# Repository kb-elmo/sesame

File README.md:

# Sesame

[![CC BY-NC-SA 4.0][cc-by-nc-sa-shield]][cc-by-nc-sa]

### Alice like ergo keyboard using only THT parts

### Partslist
 |Count|Part|Reference|LCSC Part #|
 |-|-|-|-|
 |1|ATmega32A 40 pin DIP (32L works too)|U1|C12703|
 |1|40 pin DIP socket (optional but highly recommended)|U1|C2332|
 |1|USB4085-GF-A USB Type-C socket|USB1|
 |1|500 mA polyfuse|F1|C207122|
 |2|6mm momentary push buttons|Boot,Reset|C620202|
 |1|16 MHz quartz crystal|XTAL1|C16212|
 |1|4.7 uF electrolytic capacitor|C1|C47879|
 |2|100 nF ceramic disk capacitor|C2,C3|C254092|
 |2|22 pF ceramic disk capacitor|C4,C5|C254096|
 |1|1.5 kΩ resistor|R1|C58620|
 |2|68 Ω resistor|R2,R3|C714279|
 |2|5.1 kΩ resistor|R4,R5|C714593|
 |1|10 kΩ resistor|R6|C119347|
 |2|3.6 V zener diode (DO-35 BZX55C3V6)|D1,D2|C2508|
 |66|universal switching diode (DO-35 1N4148)|D3-D68|C14516|
 
 The USB port can be found here:  
https://www.digikey.com/en/products/detail/gct/USB4085-GF-A/9859733

-----

This work is licensed under a
[Creative Commons Attribution-NonCommercial-ShareAlike 4.0 International License][cc-by-nc-sa].

[![CC BY-NC-SA 4.0][cc-by-nc-sa-image]][cc-by-nc-sa]

[cc-by-nc-sa]: http://creativecommons.org/licenses/by-nc-sa/4.0/
[cc-by-nc-sa-image]: https://licensebuttons.net/l/by-nc-sa/4.0/88x31.png
[cc-by-nc-sa-shield]: https://img.shields.io/badge/License-CC%20BY--NC--SA%204.0-lightgrey.svg

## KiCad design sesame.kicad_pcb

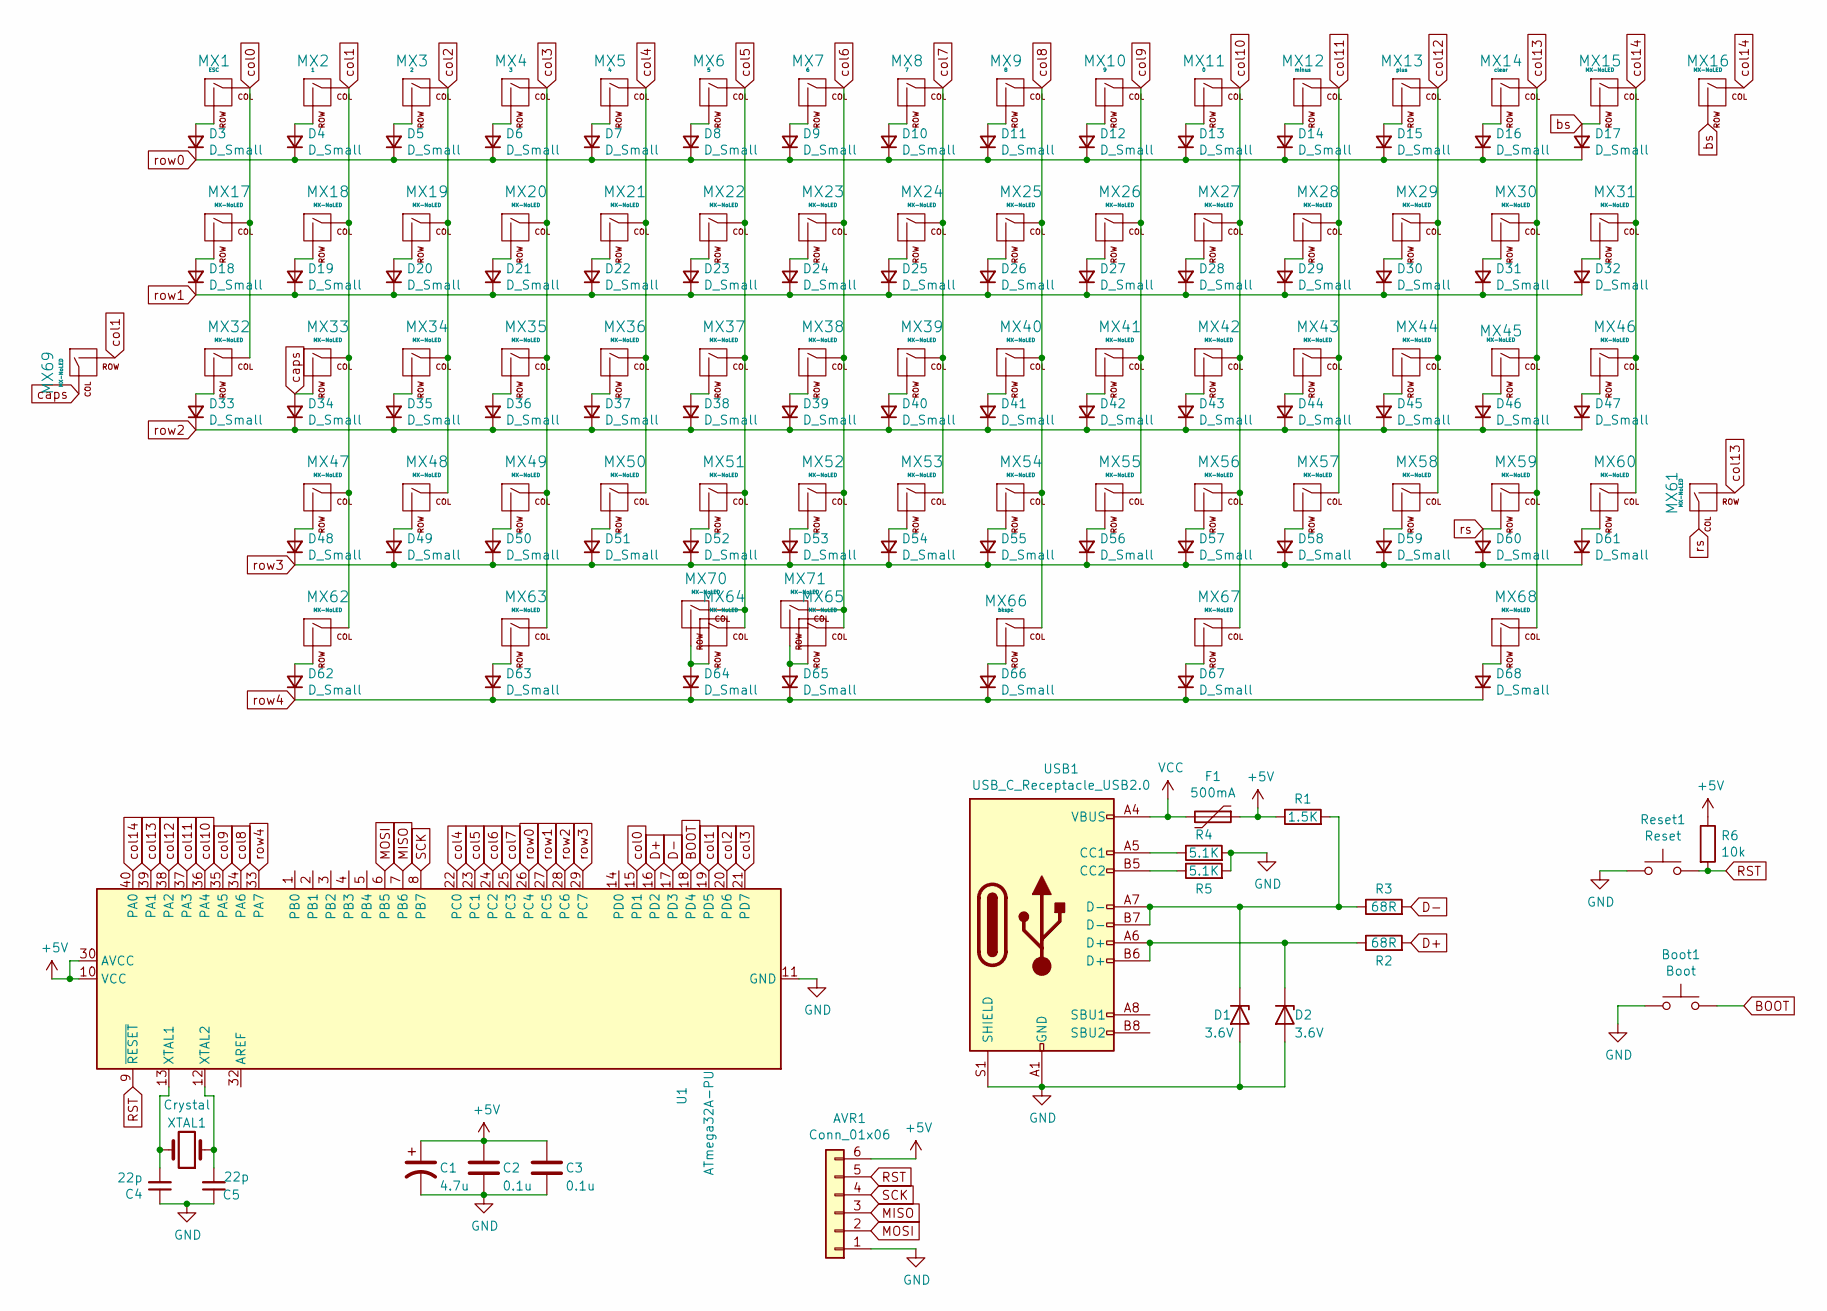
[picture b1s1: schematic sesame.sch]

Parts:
AVR1: Conn_01x06; PinHeader_1x06_P2.54mm_Vertical
Boot1: Boot; SW_PUSH_6mm
C1: 4.7u; CP_Radial_D4.0mm_P1.50mm
C2, C3: 0.1u; C_Disc_D5.0mm_W2.5mm_P5.00mm
C4, C5: 22p; C_Disc_D5.0mm_W2.5mm_P2.50mm
D1, D2: 3.6V; D_DO-35_SOD27_P7.62mm_Horizontal
D3, D4, D5, D6, D7, D8, D9, D10, D11, D12, D13, D14, D15, D16, D17, D18, D19, D20, D21, D22, D23, D24, D25, D26, D27, D28, D29, D30, D31, D32, D33, D34, D35, D36, D37, D38, D39, D40, D41, D42, D43, D44, D45, D46, D47, D48, D49, D50, D51, D52, D53, D54, D55, D56, D57, D58, D59, D60, D61, D62, D63, D64, D65, D66, D67, D68: D_Small; D_DO-35_SOD27_P7.62mm_Horizontal
F1: 500mA; Fuse_Littelfuse_395Series
MX1: ESC; MXOnly-1U-NoLED
MX2: 1; MXOnly-1U-NoLED
MX3: 2; MXOnly-1U-NoLED
MX4: 3; MXOnly-1U-NoLED
MX5: 4; MXOnly-1U-NoLED
MX6: 5; MXOnly-1U-NoLED
MX7: 6; MXOnly-1U-NoLED
MX8: 7; MXOnly-1U-NoLED
MX9: 8; MXOnly-1U-NoLED
MX10: 9; MXOnly-1U-NoLED
MX11: 0; MXOnly-1U-NoLED
MX12: minus; MXOnly-1U-NoLED
MX13: plus; MXOnly-1U-NoLED
MX14: clear; MXOnly-1U-NoLED
MX15: MX-NoLED; MXOnly-2U-NoLED
MX16, MX17, MX19, MX20, MX21, MX22, MX23, MX24, MX25, MX26, MX27, MX28, MX29, MX30, MX32, MX34, MX35, MX36, MX37, MX38, MX39, MX40, MX41, MX42, MX43, MX44, MX45, MX48, MX49, MX50, MX51, MX52, MX53, MX54, MX55, MX56, MX57, MX58, MX60, MX67, MX68, MX71: MX-NoLED; MXOnly-1U-NoLED
MX18, MX31, MX62, MX63: MX-NoLED; MXOnly-1.5U-NoLED
MX33, MX59: MX-NoLED; MXOnly-1.75U-NoLED
MX46, MX70: MX-NoLED; MXOnly-2.25U-ReversedStabilizers-NoLED
MX47: MX-NoLED; MXOnly-2.25U-NoLED
MX61: MX-NoLED; MXOnly-2.75U-NoLED
MX64: MX-NoLED; MXOnly-2U-ReversedStabilizers-NoLED
MX65, MX69: MX-NoLED; MXOnly-1.25U-NoLED
MX66: bkspc; MXOnly-2.25U-ReversedStabilizers-NoLED
R1: 1.5K; R_Axial_DIN0207_L6.3mm_D2.5mm_P10.16mm_Horizontal
R2, R3: 68R; R_Axial_DIN0207_L6.3mm_D2.5mm_P10.16mm_Horizontal
R4, R5: 5.1K; R_Axial_DIN0207_L6.3mm_D2.5mm_P10.16mm_Horizontal
R6: 10k; R_Axial_DIN0207_L6.3mm_D2.5mm_P10.16mm_Horizontal
Reset1: Reset; SW_PUSH_6mm
U1: ATmega32A-PU; DIP-40_W15.24mm
USB1: USB_C_Receptacle_USB2.0; USB_C_GCT_USB4085
XTAL1: Crystal; Crystal_HC49-4H_Vertical

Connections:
+5V: AVR1.6, C1.1, C2.1, C3.1, F1.1, R1.1, R6.1, U1.10 (VCC), U1.30 (AVCC)
BOOT: Boot1.2, U1.18 (PD4); also elsewhere on the board
D+: R2.2, U1.16 (PD2)
D-: R3.2, U1.17 (PD3)
GND: AVR1.1, Boot1.1, C1.2, C2.2, C3.2, C4.1, C5.1, D1.2 (A), D2.2 (A), R4.2, R5.2, Reset1.1, U1.11 (GND), U1.31 (GND), USB1.A1 (GND), USB1.A12 (GND), USB1.B1 (GND), USB1.B12 (GND), USB1.S1 (SHIELD); also elsewhere on the board
MISO: AVR1.3, U1.7 (PB6)
MOSI: AVR1.2, U1.6 (PB5)
unnamed: C4.2, U1.13 (XTAL1), XTAL1.2
unnamed: C5.2, U1.12 (XTAL2), XTAL1.1
unnamed: D1.1 (K), R1.2, R3.1, USB1.A7 (D-), USB1.B7 (D-)
unnamed: D2.1 (K), R2.1, USB1.A6 (D+), USB1.B6 (D+)
unnamed: D3.2 (A), MX1.2 (ROW)
unnamed: D4.2 (A), MX2.2 (ROW)
unnamed: D5.2 (A), MX3.2 (ROW)
unnamed: D6.2 (A), MX4.2 (ROW)
unnamed: D7.2 (A), MX5.2 (ROW)
unnamed: D8.2 (A), MX6.2 (ROW)
unnamed: D9.2 (A), MX7.2 (ROW)
unnamed: D10.2 (A), MX8.2 (ROW)
unnamed: D11.2 (A), MX9.2 (ROW)
unnamed: D12.2 (A), MX10.2 (ROW)
unnamed: D13.2 (A), MX11.2 (ROW)
unnamed: D14.2 (A), MX12.2 (ROW)
unnamed: D15.2 (A), MX13.2 (ROW)
unnamed: D16.2 (A), MX14.2 (ROW)
unnamed: D18.2 (A), MX17.2 (ROW)
unnamed: D19.2 (A), MX18.2 (ROW)
unnamed: D20.2 (A), MX19.2 (ROW)
unnamed: D21.2 (A), MX20.2 (ROW)
unnamed: D22.2 (A), MX21.2 (ROW)
unnamed: D23.2 (A), MX22.2 (ROW)
unnamed: D24.2 (A), MX23.2 (ROW)
unnamed: D25.2 (A), MX24.2 (ROW)
unnamed: D26.2 (A), MX25.2 (ROW)
unnamed: D27.2 (A), MX26.2 (ROW)
unnamed: D28.2 (A), MX27.2 (ROW)
unnamed: D29.2 (A), MX28.2 (ROW)
unnamed: D30.2 (A), MX29.2 (ROW)
unnamed: D31.2 (A), MX30.2 (ROW)
unnamed: D32.2 (A), MX31.2 (ROW)
unnamed: D33.2 (A), MX32.2 (ROW)
unnamed: D35.2 (A), MX34.2 (ROW)
unnamed: D36.2 (A), MX35.2 (ROW)
unnamed: D37.2 (A), MX36.2 (ROW)
unnamed: D38.2 (A), MX37.2 (ROW)
unnamed: D39.2 (A), MX38.2 (ROW)
unnamed: D40.2 (A), MX39.2 (ROW)
unnamed: D41.2 (A), MX40.2 (ROW)
unnamed: D42.2 (A), MX41.2 (ROW)
unnamed: D43.2 (A), MX42.2 (ROW)
unnamed: D44.2 (A), MX43.2 (ROW)
unnamed: D45.2 (A), MX44.2 (ROW)
unnamed: D46.2 (A), MX45.2 (ROW)
unnamed: D47.2 (A), MX46.2 (ROW)
unnamed: D48.2 (A), MX47.2 (ROW)
unnamed: D49.2 (A), MX48.2 (ROW)
unnamed: D50.2 (A), MX49.2 (ROW)
unnamed: D51.2 (A), MX50.2 (ROW)
unnamed: D52.2 (A), MX51.2 (ROW)
unnamed: D53.2 (A), MX52.2 (ROW)
unnamed: D54.2 (A), MX53.2 (ROW)
unnamed: D55.2 (A), MX54.2 (ROW)
unnamed: D56.2 (A), MX55.2 (ROW)
unnamed: D57.2 (A), MX56.2 (ROW)
unnamed: D58.2 (A), MX57.2 (ROW)
unnamed: D59.2 (A), MX58.2 (ROW)
unnamed: D61.2 (A), MX60.2 (ROW)
unnamed: D62.2 (A), MX62.2 (ROW)
unnamed: D63.2 (A), MX63.2 (ROW)
unnamed: D64.2 (A), MX64.2 (ROW), MX70.2 (ROW)
unnamed: D65.2 (A), MX65.2 (ROW), MX71.2 (ROW)
unnamed: D66.2 (A), MX66.2 (ROW)
unnamed: D67.2 (A), MX67.2 (ROW)
unnamed: D68.2 (A), MX68.2 (ROW)
unnamed: R4.1, USB1.A5 (CC1)
unnamed: R5.1, USB1.B5 (CC2)
RST: AVR1.5, R6.2, Reset1.2, U1.9 (~RESET); also elsewhere on the board
SCK: AVR1.4, U1.8 (PB7)
VCC: F1.2, USB1.A4 (VBUS), USB1.A9 (VBUS), USB1.B4 (VBUS), USB1.B9 (VBUS)
bs: D17.2 (A), MX15.2 (ROW), MX16.2 (ROW)
caps: D34.2 (A), MX33.2 (ROW), MX69.1 (COL)
col0: MX1.1 (COL), MX17.1 (COL), MX32.1 (COL), U1.15 (PD1)
col1: MX2.1 (COL), MX18.1 (COL), MX33.1 (COL), MX47.1 (COL), MX62.1 (COL), MX69.2 (ROW), U1.19 (PD5)
col2: MX3.1 (COL), MX19.1 (COL), MX34.1 (COL), MX48.1 (COL), U1.20 (PD6)
col3: MX4.1 (COL), MX20.1 (COL), MX35.1 (COL), MX49.1 (COL), MX63.1 (COL), U1.21 (PD7)
col4: MX5.1 (COL), MX21.1 (COL), MX36.1 (COL), MX50.1 (COL), U1.22 (PC0)
col5: MX6.1 (COL), MX22.1 (COL), MX37.1 (COL), MX51.1 (COL), MX64.1 (COL), MX70.1 (COL), U1.23 (PC1)
col6: MX7.1 (COL), MX23.1 (COL), MX38.1 (COL), MX52.1 (COL), MX65.1 (COL), MX71.1 (COL), U1.24 (PC2)
col7: MX8.1 (COL), MX24.1 (COL), MX39.1 (COL), MX53.1 (COL), U1.25 (PC3)
col8: MX9.1 (COL), MX25.1 (COL), MX40.1 (COL), MX54.1 (COL), MX66.1 (COL), U1.34 (PA6)
col9: MX10.1 (COL), MX26.1 (COL), MX41.1 (COL), MX55.1 (COL), U1.35 (PA5)
col10: MX11.1 (COL), MX27.1 (COL), MX42.1 (COL), MX56.1 (COL), MX67.1 (COL), U1.36 (PA4)
col11: MX12.1 (COL), MX28.1 (COL), MX43.1 (COL), MX57.1 (COL), U1.37 (PA3)
col12: MX13.1 (COL), MX29.1 (COL), MX44.1 (COL), MX58.1 (COL), U1.38 (PA2)
col13: MX14.1 (COL), MX30.1 (COL), MX45.1 (COL), MX59.1 (COL), MX61.2 (ROW), MX68.1 (COL), U1.39 (PA1)
col14: MX15.1 (COL), MX16.1 (COL), MX31.1 (COL), MX46.1 (COL), MX60.1 (COL), U1.40 (PA0)
row0: D3.1 (K), D4.1 (K), D5.1 (K), D6.1 (K), D7.1 (K), D8.1 (K), D9.1 (K), D10.1 (K), D11.1 (K), D12.1 (K), D13.1 (K), D14.1 (K), D15.1 (K), D16.1 (K), D17.1 (K), U1.26 (PC4)
row1: D18.1 (K), D19.1 (K), D20.1 (K), D21.1 (K), D22.1 (K), D23.1 (K), D24.1 (K), D25.1 (K), D26.1 (K), D27.1 (K), D28.1 (K), D29.1 (K), D30.1 (K), D31.1 (K), D32.1 (K), U1.27 (PC5)
row2: D33.1 (K), D34.1 (K), D35.1 (K), D36.1 (K), D37.1 (K), D38.1 (K), D39.1 (K), D40.1 (K), D41.1 (K), D42.1 (K), D43.1 (K), D44.1 (K), D45.1 (K), D46.1 (K), D47.1 (K), U1.28 (PC6)
row3: D48.1 (K), D49.1 (K), D50.1 (K), D51.1 (K), D52.1 (K), D53.1 (K), D54.1 (K), D55.1 (K), D56.1 (K), D57.1 (K), D58.1 (K), D59.1 (K), D60.1 (K), D61.1 (K), U1.29 (PC7)
row4: D62.1 (K), D63.1 (K), D64.1 (K), D65.1 (K), D66.1 (K), D67.1 (K), D68.1 (K), U1.33 (PA7)
rs: D60.2 (A), MX59.2 (ROW), MX61.1 (COL)

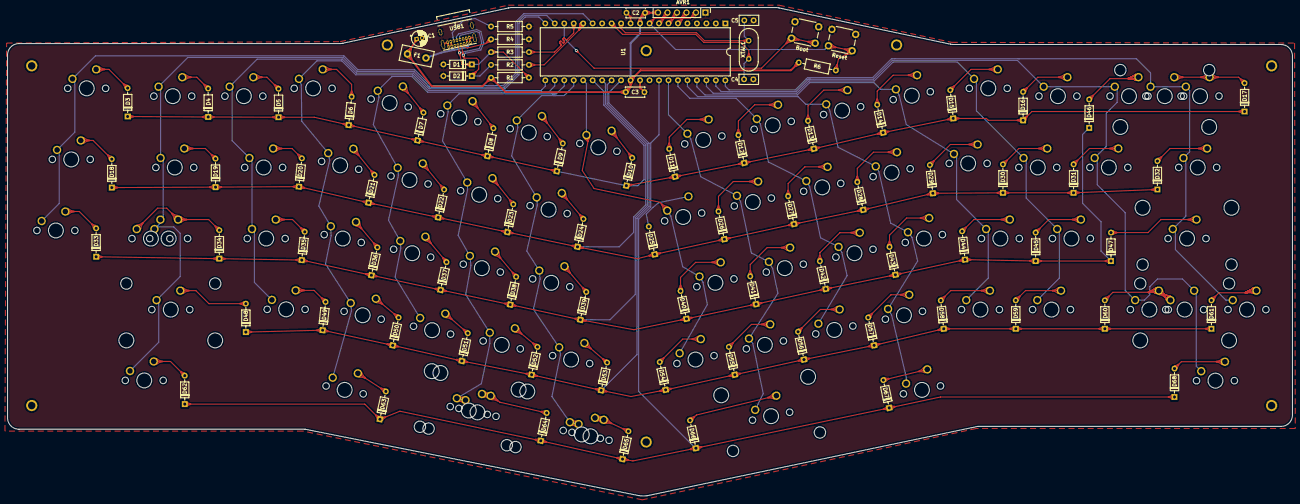
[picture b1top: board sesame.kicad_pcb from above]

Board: 2 copper layers, 344.4 x 130.9 mm, 157 parts (0 on the bottom side), 102 nets.

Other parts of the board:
Boot: Boot; SW_PUSH_6mm
Reset: Reset; SW_PUSH_6mm

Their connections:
BOOT: Boot.2; also elsewhere on the board
GND: Boot.1, Reset.1; also elsewhere on the board
RST: Reset.2; also elsewhere on the board

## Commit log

2020-07-11 Update LICENSE
2020-07-21 fix layout and add firmware
2020-07-21 remove misplaced files
2020-07-22 fix diode placement
2020-07-27 added extras and qmk info.json
2020-07-30 fix ground plane
2020-07-30 update switchplate
2020-07-30 add teardrops
2020-08-02 update plate and add feet to bottom
2020-08-02 add stepped caps support
2020-08-10 minor design changes
2020-08-30 fix routing error
2020-09-28 Add VIA support
2020-09-28 update qmk formatting stuff
2020-10-02 remove wrong case files
2020-10-18 fix screwhole position on backplate
2020-10-19 just updating the heading to reflect source of data
    noting my changes
2020-10-20 Update README.md
    minor typo correction
2020-10-20 add buildguide
2020-12-05 fixed sizing issue and added svg
    i tried laser cutting the .dxf but had sizing issues - resaved it in qcad and exported an svg suitable for cutting.
2021-01-16 add acrylic layer case
2021-01-16 update case
2021-01-16 update case (again)
2021-01-18 update gerbers to latest kicad version defaults
2021-02-03 update acrylic case
2021-02-20 fix top frame
2021-02-22 update gerbers
2021-03-07 feat(docs): Add LCSC Part Numbers to Part Table
2021-03-08 Update README.md
    add link to the USB port part
2021-03-09 change picture
2021-04-17 add 2.25u left space support and update caps to use cftkb footprints
2021-04-17 fixes
2021-04-17 update LCSC part no.
2021-04-17 fix silkscreen
2021-04-17 fix silkscreen (again)
2021-04-17 Updated readme with octopart link to USB connector
2021-05-14 Update image
2021-12-09 change fuse LCSC part
